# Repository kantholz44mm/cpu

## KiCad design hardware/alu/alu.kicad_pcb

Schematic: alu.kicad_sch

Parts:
C1, C2, C3, C4, C5, C6, C7, C8, C9, C10, C11, C12, C13, C14, C15, C16, C17, C18, C19, C20, C21, C22, C23, C24, C25, C26, C27, C28, C29, C30, C31, C32, C33, C34, C35, C40, C41, C42, C43, C44, C45, C46, C47, C50, C51, C52, C53, C54, C55, C56, C57, C58, C59, C60, C61, C62, C63, C64, C65, C66, C67, C68, C69, C70, C71, C72, C73, C77, C78, C79, C80, C81, C82, C83, C84, C85, C90, C91, C92, C93, C94, C95: 330nF; C_0402_1005Metric; LCSC C77020
C86, C87, C88, C89: 22pF; C_Radial_D5.0mm_H11.0mm_P2.00mm; not fitted
D30, D31, D32, D33, D34, D35, D36, D37, D38, D39, D40, D41, D42, D43, D44, D45, D46, D47, D48, D49, D50, D51, D52, D63, D89, D90, D91, D92, D93, D137, D138, D139, D140, D141, D142, D143, D144, D145, D146, D147, D148, D149, D150: LED; LED_0402_1005Metric; LCSC C965793
D124, D125, D126, D127, D128, D129, D130, D131: D_Schottky; DO35_Packed; not fitted
H1, H2, H3: MountingHole_Pad; MountingHole_3.2mm_M3_ISO7380_Pad_TopBottom
J8: Conn_02x24_Odd_Even; PinHeader_2x24_P2.54mm_Horizontal; not fitted
Q93, Q96, Q98, Q100, Q102, Q104, Q106, Q108, Q110, Q112, Q114, Q116, Q118, Q120, Q122, Q124, Q126, Q128, Q130, Q132, Q134, Q136, Q138, Q140, Q142, Q144, Q146, Q148, Q150, Q152, Q154, Q156, Q158, Q160, Q162, Q164, Q166, Q168, Q170, Q172, Q174, Q176: IRLML6402; SOT-23; LCSC C2886430
Q94, Q95, Q97, Q99, Q101, Q103, Q105, Q107, Q109, Q111, Q113, Q115, Q117, Q119, Q121, Q123, Q125, Q127, Q129, Q131, Q133, Q135, Q137, Q139, Q141, Q143, Q145, Q147, Q149, Q151, Q153, Q155, Q157, Q159, Q161, Q163, Q165, Q167, Q169, Q171, Q173, Q175: IRLML6244; SOT-23; LCSC C5123965
R1, R2, R3, R4, R5, R6, R7, R8, R9, R10, R11, R12, R13, R14, R15, R16, R17, R18, R19, R20, R21: 100K; R_0402_1005Metric; LCSC C60491
R107, R108, R109, R110, R111, R112, R113, R114, R115, R116, R117, R118, R119, R120, R121, R122, R123, R124, R125, R126, R127, R128, R129, R130, R131, R132, R133, R134, R135, R136, R137, R138, R139, R140, R141, R142, R143, R144, R145, R146, R147, R148, R149, R150, R151, R152, R153, R154, R155, R156, R157, R158, R159, R160, R161, R162, R163, R164, R165, R166, R167, R168, R169, R170, R171, R172, R173, R174, R175, R176, R177, R178, R179, R180, R181, R182, R183, R184, R185, R186, R187, R188, R189, R190, R191, R192: 1000; R_0402_1005Metric; LCSC C106235
U1, U2, U3, U4, U5, U6, U7, U8, U9, U10, U11, U12, U13, U14, U15, U16, U17, U18, U19, U20, U21, U22, U23, U24, U25, U26, U27, U28, U29, U30, U31, U32, U33, U34, U35, U36, U37, U38, U39, U40, U41, U44, U45, U46, U47, U48, U49, U56, U57, U64, U65, U72, U73, U74, U75, U83, U87: 74HC00; SOIC-14_3.9x8.7mm_P1.27mm; LCSC C5586
U42, U43, U50, U51, U52, U53, U54, U55, U58, U59, U60, U61, U62, U63, U66, U67, U71, U84, U85, U86, U88, U89, U90, U91: 74LS157; SOIC-16_3.9x9.9mm_P1.27mm; LCSC C6823
U68: 74HCT238; SOIC-16_3.9x9.9mm_P1.27mm; LCSC C5620

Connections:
+5V: C1.1, C2.1, C3.1, C4.1, C5.1, C6.1, C7.1, C8.1, C9.1, C10.1, C11.1, C12.1, C13.1, C14.1, C15.1, C16.1, C17.1, C18.1, C19.1, C20.1, C21.1, C22.1, C23.1, C24.1, C25.1, C26.1, C27.1, C28.1, C29.1, C30.1, C31.1, C32.1, C33.1, C34.1, C35.1, C40.1, C41.1, C42.1, C43.1, C44.1, C45.1, C46.1, C47.1, C50.1, C51.1, C52.1, C53.1, C54.1, C55.1, C56.1, C57.1, C58.1, C59.1, C60.1, C61.1, C62.1, C63.1, C64.1, C65.1, C66.1, C67.1, C68.1, C69.1, C70.1, C71.1, C72.1, C73.1, C77.1, C78.1, C79.1, C80.1, C81.1, C82.1, C83.1, C84.1, C85.1, C86.1, C87.1, C88.1, C89.1, C90.1, C91.1, C92.1, C93.1, C94.1, C95.1, D52.2 (A), J8.44, J8.46, Q93.2 (S), Q96.2 (S), Q98.2 (S), Q100.2 (S), Q102.2 (S), Q104.2 (S), Q106.2 (S), Q108.2 (S), Q110.2 (S), Q112.2 (S), Q114.2 (S), Q116.2 (S), Q118.2 (S), Q120.2 (S), Q122.2 (S), Q124.2 (S), Q126.2 (S), Q128.2 (S), Q130.2 (S), Q132.2 (S), Q134.2 (S), Q136.2 (S), Q138.2 (S), Q140.2 (S), Q142.2 (S), Q144.2 (S), Q146.2 (S), Q148.2 (S), Q150.2 (S), Q152.2 (S), Q154.2 (S), Q156.2 (S), Q158.2 (S), Q160.2 (S), Q162.2 (S), Q164.2 (S), Q166.2 (S), Q168.2 (S), Q170.2 (S), Q172.2 (S), Q174.2 (S), Q176.2 (S), R107.2, R108.2, R109.2, R110.2, R111.2, R112.2, R113.2, R114.2, R115.2, R116.2, R117.2, R118.2, R119.2, R120.2, R121.2, R122.2, R123.2, R124.2, R125.2, R126.2, R127.2, R128.2, R129.2, R130.2, R131.2, R132.2, R133.2, R134.2, R135.2, R136.2, R137.2, R138.2, R139.2, R140.2, R141.2, R142.2, R144.2, R146.2, R184.2, R186.2, R188.2, R190.2, U1.14 (VCC), U2.14 (VCC), U3.14 (VCC), U4.14 (VCC), U5.14 (VCC), U6.14 (VCC), U7.14 (VCC), U8.14 (VCC), U9.14 (VCC), U10.14 (VCC), U11.14 (VCC), U12.14 (VCC), U13.14 (VCC), U14.14 (VCC), U15.14 (VCC), U16.14 (VCC), U17.14 (VCC), U18.14 (VCC), U19.14 (VCC), U20.14 (VCC), U21.14 (VCC), U22.14 (VCC), U23.14 (VCC), U24.14 (VCC), U25.14 (VCC), U26.14 (VCC), U27.14 (VCC), U28.14 (VCC), U29.14 (VCC), U30.14 (VCC), U31.14 (VCC), U32.14 (VCC), U33.14 (VCC), U34.14 (VCC), U35.14 (VCC), U36.14 (VCC), U37.14 (VCC), U38.14 (VCC), U39.14 (VCC), U40.14 (VCC), U41.14 (VCC), U42.16 (VCC), U43.16 (VCC), U44.14 (VCC), U45.14 (VCC), U46.14 (VCC), U47.14 (VCC), U48.14 (VCC), U49.14 (VCC), U50.16 (VCC), U51.16 (VCC), U52.16 (VCC), U53.16 (VCC), U54.16 (VCC), U55.16 (VCC), U56.14 (VCC), U57.14 (VCC), U58.16 (VCC), U59.16 (VCC), U60.16 (VCC), U61.16 (VCC), U62.16 (VCC), U63.16 (VCC), U64.14 (VCC), U65.14 (VCC), U66.16 (VCC), U67.16 (VCC), U68.6 (E3), U68.16 (VCC), U71.16 (VCC), U72.14 (VCC), U73.14 (VCC), U74.14 (VCC), U75.14 (VCC), U83.14 (VCC), U84.16 (VCC), U85.16 (VCC), U86.16 (VCC), U87.14 (VCC), U88.16 (VCC), U89.16 (VCC), U90.16 (VCC), U91.16 (VCC)
/A0: J8.3, Q94.1 (G), R1.1
/A1: J8.5, Q95.1 (G), R3.1
/A2: J8.7, Q97.1 (G), R2.1
/A3: J8.9, Q99.1 (G), R4.1
/A4: J8.13, Q101.1 (G), R5.1
/A5: J8.15, Q103.1 (G), R6.1
/A6: J8.17, Q105.1 (G), R7.1
/A7: J8.19, Q107.1 (G), R8.1
/B0: J8.4, Q109.1 (G), R21.1
/B1: J8.6, Q111.1 (G), R20.1
/B2: J8.8, Q113.1 (G), R19.1
/B3: J8.10, Q115.1 (G), R18.1
/B4: J8.14, Q117.1 (G), R17.1
/B5: J8.16, Q119.1 (G), R16.1
/B6: J8.18, Q121.1 (G), R15.1
/B7: J8.20, Q123.1 (G), R14.1
/CEN: J8.35, Q125.1 (G), R12.1
/CIN: J8.33, Q127.1 (G), R13.1
/COUT: D50.2 (A), J8.27, Q174.3 (D)
/IA0: D35.2 (A), Q93.3 (D), U1.1, U1.4, U36.1, U36.2, U44.1, U44.4, U54.2 (I0a), U54.6 (I1b), U62.2 (I0a), U87.10
/IA1: D36.2 (A), Q96.3 (D), U5.1, U5.4, U37.1, U37.2, U45.1, U45.4, U54.5 (I0b), U54.10 (I1c), U62.3 (I1a), U62.5 (I0b)
/IA2: D37.2 (A), Q98.3 (D), U9.1, U9.4, U38.1, U38.2, U46.1, U46.4, U54.11 (I0c), U54.13 (I1d), U62.6 (I1b), U62.11 (I0c)
/IA3: D38.2 (A), Q100.3 (D), U13.1, U13.4, U39.1, U39.2, U47.1, U47.4, U54.14 (I0d), U55.3 (I1a), U62.10 (I1c), U62.14 (I0d)
/IA4: D39.2 (A), Q102.3 (D), U17.1, U17.4, U40.1, U40.2, U48.1, U48.4, U55.2 (I0a), U55.6 (I1b), U62.13 (I1d), U63.2 (I0a)
/IA5: D40.2 (A), Q104.3 (D), U21.1, U21.4, U55.5 (I0b), U55.10 (I1c), U56.1, U56.2, U63.3 (I1a), U63.5 (I0b), U64.1, U64.4
/IA6: D41.2 (A), Q106.3 (D), U25.1, U25.4, U41.1, U41.2, U49.1, U49.4, U55.11 (I0c), U55.13 (I1d), U63.6 (I1b), U63.11 (I0c)
/IA7: D42.2 (A), Q108.3 (D), U29.1, U29.4, U55.14 (I0d), U57.1, U57.2, U63.10 (I1c), U63.14 (I0d), U65.1, U65.4, U87.4
/IB0: D141.2 (A), Q110.3 (D), U4.1, U4.4, U36.4, U36.5, U44.2, U44.10, U54.1 (S), U55.1 (S), U62.1 (S), U63.1 (S)
/IB1: D140.2 (A), Q112.3 (D), U8.1, U8.4, U37.4, U37.5, U45.2, U45.10, U58.1 (S), U59.1 (S), U66.1 (S), U67.1 (S)
/IB2: D139.2 (A), Q114.3 (D), U12.1, U12.4, U38.4, U38.5, U46.2, U46.10, U60.1 (S), U61.1 (S), U71.1 (S), U84.1 (S)
/IB3: D138.2 (A), Q116.3 (D), U16.1, U16.4, U39.4, U39.5, U47.2, U47.10
/IB4: D137.2 (A), Q118.3 (D), U20.1, U20.4, U40.4, U40.5, U48.2, U48.10
/IB5: D45.2 (A), Q120.3 (D), U24.1, U24.4, U56.4, U56.5, U64.2, U64.10
/IB6: D44.2 (A), Q122.3 (D), U28.1, U28.4, U41.4, U41.5, U49.2, U49.10
/IB7: D43.2 (A), Q124.3 (D), U32.1, U32.4, U57.4, U57.5, U65.2, U65.10
/ICEN: D33.2 (A), Q126.3 (D), U83.2
/ICIN: D34.2 (A), Q128.3 (D), U83.1
/ICRY: D144.2 (A), Q152.3 (D), U33.1, U33.4, U54.3 (I1a), U58.3 (I1a), U58.6 (I1b), U60.3 (I1a), U60.6 (I1b), U60.10 (I1c), U60.13 (I1d), U63.13 (I1d), U67.10 (I1c), U67.13 (I1d), U84.3 (I1a), U84.6 (I1b), U84.10 (I1c), U84.13 (I1d)
/IOP0: D30.2 (A), Q130.3 (D), U4.2, U4.10, U8.2, U8.10, U12.2, U12.10, U16.2, U16.10, U20.2, U20.10, U24.2, U24.10, U28.2, U28.10, U32.2, U32.10, U33.2, U33.10, U35.2, U35.10, U42.1 (S), U43.1 (S), U51.1 (S), U53.1 (S), U68.1 (A0), U85.1 (S), U86.1 (S), U87.1, U87.2, U87.9
/IOP1: D31.2 (A), Q132.3 (D), U50.1 (S), U52.1 (S), U68.2 (A1), U72.10, U72.12, U72.13, U75.4, U75.5, U90.1 (S), U91.1 (S)
/IOP2: D32.2 (A), Q134.3 (D), U68.3 (A2), U73.10, U73.12, U73.13, U75.9, U75.10, U88.1 (S), U89.1 (S)
/IOPSEL0: D63.2 (A), Q136.3 (D)
/IOPSEL1: D89.2 (A), Q138.3 (D)
/IOPSEL2: D90.2 (A), Q140.3 (D)
/IOPSEL3: D91.2 (A), Q142.3 (D)
/IOPSEL4: D92.2 (A), Q144.3 (D)
/IOPSEL5: D93.2 (A), Q146.3 (D)
/IOPSEL6: D142.2 (A), Q148.3 (D)
/IOPSEL7: D143.2 (A), Q150.3 (D)
/NEG: D49.2 (A), J8.25, Q172.3 (D)
/OP0: J8.39, Q129.1 (G), R9.1
/OP1: J8.41, Q131.1 (G), R10.1
/OP2: J8.43, Q133.1 (G), R11.1
/ORES0: D48.2 (A), D128.2 (A), J8.24, Q168.3 (D)
/ORES1: D47.2 (A), D129.2 (A), J8.26, Q166.3 (D)
/ORES2: D46.2 (A), D130.2 (A), J8.28, Q164.3 (D)
/ORES3: D131.2 (A), D149.2 (A), J8.30, Q162.3 (D)
/ORES4: D127.2 (A), D148.2 (A), J8.34, Q160.3 (D)
/ORES5: D126.2 (A), D147.2 (A), J8.36, Q158.3 (D)
/ORES6: D125.2 (A), D146.2 (A), J8.38, Q156.3 (D)
/ORES7: D124.2 (A), D145.2 (A), J8.40, Q154.3 (D), Q171.1 (G)
/OVF: D51.2 (A), J8.29, Q176.3 (D)
/ZERO: D150.2 (A), J8.23, Q170.3 (D)
GND: C1.2, C2.2, C3.2, C4.2, C5.2, C6.2, C7.2, C8.2, C9.2, C10.2, C11.2, C12.2, C13.2, C14.2, C15.2, C16.2, C17.2, C18.2, C19.2, C20.2, C21.2, C22.2, C23.2, C24.2, C25.2, C26.2, C27.2, C28.2, C29.2, C30.2, C31.2, C32.2, C33.2, C34.2, C35.2, C40.2, C41.2, C42.2, C43.2, C44.2, C45.2, C46.2, C47.2, C50.2, C51.2, C52.2, C53.2, C54.2, C55.2, C56.2, C57.2, C58.2, C59.2, C60.2, C61.2, C62.2, C63.2, C64.2, C65.2, C66.2, C67.2, C68.2, C69.2, C70.2, C71.2, C72.2, C73.2, C77.2, C78.2, C79.2, C80.2, C81.2, C82.2, C83.2, C84.2, C85.2, C86.2, C87.2, C88.2, C89.2, C90.2, C91.2, C92.2, C93.2, C94.2, C95.2, H1.1, H2.1, H3.1, J8.1, J8.2, J8.11, J8.12, J8.21, J8.22, J8.31, J8.32, J8.37, J8.42, J8.45, J8.47, J8.48, Q94.2 (S), Q95.2 (S), Q97.2 (S), Q99.2 (S), Q101.2 (S), Q103.2 (S), Q105.2 (S), Q107.2 (S), Q109.2 (S), Q111.2 (S), Q113.2 (S), Q115.2 (S), Q117.2 (S), Q119.2 (S), Q121.2 (S), Q123.2 (S), Q125.2 (S), Q127.2 (S), Q129.2 (S), Q131.2 (S), Q133.2 (S), Q135.2 (S), Q137.2 (S), Q139.2 (S), Q141.2 (S), Q143.2 (S), Q145.2 (S), Q147.2 (S), Q149.2 (S), Q151.2 (S), Q153.2 (S), Q155.2 (S), Q157.2 (S), Q159.2 (S), Q161.2 (S), Q163.2 (S), Q165.2 (S), Q167.2 (S), Q169.2 (S), Q171.2 (S), Q173.2 (S), Q175.2 (S), R1.2, R2.2, R3.2, R4.2, R5.2, R6.2, R7.2, R8.2, R9.2, R10.2, R11.2, R12.2, R13.2, R14.2, R15.2, R16.2, R17.2, R18.2, R19.2, R20.2, R21.2, R143.1, R145.1, R147.1, R148.1, R149.1, R150.1, R151.1, R152.1, R153.1, R154.1, R155.1, R156.1, R157.1, R158.1, R159.1, R160.1, R161.1, R162.1, R163.1, R164.1, R165.1, R166.1, R167.1, R168.1, R169.1, R170.1, R171.1, R172.1, R173.1, R174.1, R175.1, R176.1, R177.1, R178.1, R179.1, R180.1, R181.1, R182.1, R183.1, R185.1, R187.1, R189.1, R191.1, R192.1, U1.7 (GND), U2.7 (GND), U3.4, U3.5, U3.7 (GND), U3.9, U3.10, U3.12, U3.13, U4.7 (GND), U5.7 (GND), U6.7 (GND), U7.4, U7.5, U7.7 (GND), U7.9, U7.10, U7.12, U7.13, U8.7 (GND), U9.7 (GND), U10.7 (GND), U11.4, U11.5, U11.7 (GND), U11.9, U11.10, U11.12, U11.13, U12.7 (GND), U13.7 (GND), U14.7 (GND), U15.4, U15.5, U15.7 (GND), U15.9, U15.10, U15.12, U15.13, U16.7 (GND), U17.7 (GND), U18.7 (GND), U19.4, U19.5, U19.7 (GND), U19.9, U19.10, U19.12, U19.13, U20.7 (GND), U21.7 (GND), U22.7 (GND), U23.4, U23.5, U23.7 (GND), U23.9, U23.10, U23.12, U23.13, U24.7 (GND), U25.7 (GND), U26.7 (GND), U27.4, U27.5, U27.7 (GND), U27.9, U27.10, U27.12, U27.13, U28.7 (GND), U29.7 (GND), U30.7 (GND), U31.4, U31.5, U31.7 (GND), U31.9, U31.10, U31.12, U31.13, U32.7 (GND), U33.7 (GND), U34.7 (GND), U35.7 (GND), U36.7 (GND), U37.7 (GND), U38.7 (GND), U39.7 (GND), U40.7 (GND), U41.7 (GND), U42.8 (GND), U42.15 (E), U43.8 (GND), U43.15 (E), U44.7 (GND), U45.7 (GND), U46.7 (GND), U47.7 (GND), U48.7 (GND), U49.7 (GND), U50.8 (GND), U50.15 (E), U51.8 (GND), U51.15 (E), U52.8 (GND), U52.15 (E), U53.8 (GND), U53.15 (E), U54.8 (GND), U54.15 (E), U55.8 (GND), U55.15 (E), U56.7 (GND), U57.7 (GND), U58.8 (GND), U58.15 (E), U59.8 (GND), U59.15 (E), U60.8 (GND), U60.15 (E), U61.8 (GND), U61.15 (E), U62.8 (GND), U62.15 (E), U63.8 (GND), U63.15 (E), U64.7 (GND), U65.7 (GND), U66.8 (GND), U66.15 (E), U67.8 (GND), U67.15 (E), U68.4 (~E1), U68.5 (~E2), U68.8 (GND), U71.8 (GND), U71.15 (E), U72.7 (GND), U73.7 (GND), U73.9, U74.7 (GND), U74.9, U75.7 (GND), U83.7 (GND), U83.9, U83.10, U83.12, U83.13, U84.8 (GND), U84.15 (E), U85.8 (GND), U85.15 (E), U86.8 (GND), U86.15 (E), U87.7 (GND), U88.8 (GND), U88.15 (E), U89.8 (GND), U89.15 (E), U90.8 (GND), U90.15 (E), U91.8 (GND), U91.15 (E)
unnamed: D30.1 (K), R143.2
unnamed: D31.1 (K), R145.2
unnamed: D32.1 (K), R147.2
unnamed: D33.1 (K), R148.2
unnamed: D34.1 (K), R149.2
unnamed: D35.1 (K), R150.2
unnamed: D36.1 (K), R151.2
unnamed: D37.1 (K), R152.2
unnamed: D38.1 (K), R153.2
unnamed: D39.1 (K), R154.2
unnamed: D40.1 (K), R155.2
unnamed: D41.1 (K), R156.2
unnamed: D42.1 (K), R157.2
unnamed: D43.1 (K), R158.2
unnamed: D44.1 (K), R159.2
unnamed: D45.1 (K), R160.2
unnamed: D46.1 (K), R180.2
unnamed: D47.1 (K), R181.2
unnamed: D48.1 (K), R182.2
unnamed: D49.1 (K), R187.2
unnamed: D50.1 (K), R189.2
unnamed: D51.1 (K), R191.2
unnamed: D52.1 (K), R192.2
unnamed: D63.1 (K), R166.2
unnamed: D89.1 (K), R167.2
unnamed: D90.1 (K), R168.2
unnamed: D91.1 (K), R169.2
unnamed: D92.1 (K), R170.2
unnamed: D93.1 (K), R171.2
unnamed: D124.1 (K), D125.1 (K), D126.1 (K), D127.1 (K), D128.1 (K), D129.1 (K), D130.1 (K), D131.1 (K), R183.2, U75.12, U75.13
unnamed: D137.1 (K), R161.2
unnamed: D138.1 (K), R162.2
unnamed: D139.1 (K), R163.2
unnamed: D140.1 (K), R164.2
unnamed: D141.1 (K), R165.2
unnamed: D142.1 (K), R172.2
unnamed: D143.1 (K), R173.2
unnamed: D144.1 (K), R174.2
unnamed: D145.1 (K), R175.2
unnamed: D146.1 (K), R176.2
unnamed: D147.1 (K), R177.2
unnamed: D148.1 (K), R178.2
unnamed: D149.1 (K), R179.2
unnamed: D150.1 (K), R185.2
unnamed: Q93.1 (G), Q94.3 (D), R107.1
unnamed: Q95.3 (D), Q96.1 (G), R108.1
unnamed: Q97.3 (D), Q98.1 (G), R110.1
unnamed: Q99.3 (D), Q100.1 (G), R112.1
unnamed: Q101.3 (D), Q102.1 (G), R114.1
unnamed: Q103.3 (D), Q104.1 (G), R116.1
unnamed: Q105.3 (D), Q106.1 (G), R118.1
unnamed: Q107.3 (D), Q108.1 (G), R120.1
unnamed: Q109.3 (D), Q110.1 (G), R122.1
unnamed: Q111.3 (D), Q112.1 (G), R124.1
unnamed: Q113.3 (D), Q114.1 (G), R126.1
unnamed: Q115.3 (D), Q116.1 (G), R128.1
unnamed: Q117.3 (D), Q118.1 (G), R130.1
unnamed: Q119.3 (D), Q120.1 (G), R132.1
unnamed: Q121.3 (D), Q122.1 (G), R134.1
unnamed: Q123.3 (D), Q124.1 (G), R136.1
unnamed: Q125.3 (D), Q126.1 (G), R138.1
unnamed: Q127.3 (D), Q128.1 (G), R140.1
unnamed: Q129.3 (D), Q130.1 (G), R142.1
unnamed: Q131.3 (D), Q132.1 (G), R144.1
unnamed: Q133.3 (D), Q134.1 (G), R146.1
unnamed: Q135.3 (D), Q136.1 (G), R109.1
unnamed: Q135.1 (G), U68.15 (Y0)
unnamed: Q137.3 (D), Q138.1 (G), R111.1
unnamed: Q137.1 (G), U68.14 (Y1)
unnamed: Q139.3 (D), Q140.1 (G), R113.1
unnamed: Q139.1 (G), U68.13 (Y2)
unnamed: Q141.3 (D), Q142.1 (G), R115.1
unnamed: Q141.1 (G), U68.12 (Y3)
unnamed: Q143.3 (D), Q144.1 (G), R117.1
unnamed: Q143.1 (G), U68.11 (Y4)
unnamed: Q145.3 (D), Q146.1 (G), R119.1
unnamed: Q145.1 (G), U68.10 (Y5)
unnamed: Q147.3 (D), Q148.1 (G), R121.1
unnamed: Q147.1 (G), U68.9 (Y6)
unnamed: Q149.3 (D), Q150.1 (G), R123.1
unnamed: Q149.1 (G), U68.7 (Y7)
unnamed: Q151.3 (D), Q152.1 (G), R141.1
unnamed: Q151.1 (G), U83.6
unnamed: Q153.3 (D), Q154.1 (G), R125.1
unnamed: Q153.1 (G), U89.12 (Zd)
unnamed: Q155.3 (D), Q156.1 (G), R127.1
unnamed: Q155.1 (G), U89.9 (Zc)
unnamed: Q157.3 (D), Q158.1 (G), R129.1
unnamed: Q157.1 (G), U89.7 (Zb)
unnamed: Q159.3 (D), Q160.1 (G), R131.1
unnamed: Q159.1 (G), U89.4 (Za)
unnamed: Q161.3 (D), Q162.1 (G), R133.1
unnamed: Q161.1 (G), U88.12 (Zd)
unnamed: Q163.3 (D), Q164.1 (G), R135.1
unnamed: Q163.1 (G), U88.9 (Zc)
unnamed: Q165.3 (D), Q166.1 (G), R137.1
unnamed: Q165.1 (G), U88.7 (Zb)
unnamed: Q167.3 (D), Q168.1 (G), R139.1
unnamed: Q167.1 (G), U88.4 (Za)
unnamed: Q169.3 (D), Q170.1 (G), R184.1
unnamed: Q169.1 (G), U75.11
unnamed: Q171.3 (D), Q172.1 (G), R186.1
unnamed: Q173.3 (D), Q174.1 (G), R188.1
unnamed: Q173.1 (G), U73.3
unnamed: Q175.3 (D), Q176.1 (G), R190.1
unnamed: Q175.1 (G), U74.3
unnamed: U1.3, U1.5, U1.9, U3.2
unnamed: U1.2, U1.10, U4.11
unnamed: U1.11, U2.1, U2.4
unnamed: U1.6, U1.12
unnamed: U1.8, U1.13
unnamed: U2.3, U2.5, U2.9, U3.1
unnamed: U2.2, U2.10, U33.11
unnamed: U2.6, U2.12
unnamed: U2.8, U2.13
unnamed: U3.3, U6.2, U6.10
unnamed: U4.3, U4.5, U4.9
unnamed: U4.6, U4.12
unnamed: U4.8, U4.13
unnamed: U5.3, U5.5, U5.9, U7.2
unnamed: U5.2, U5.10, U8.11
unnamed: U5.11, U6.1, U6.4
unnamed: U5.6, U5.12
unnamed: U5.8, U5.13
unnamed: U6.3, U6.5, U6.9, U7.1
unnamed: U6.6, U6.12
unnamed: U6.8, U6.13
unnamed: U8.3, U8.5, U8.9
unnamed: U8.6, U8.12
unnamed: U8.8, U8.13
unnamed: U9.6, U9.12
unnamed: U9.8, U9.13
unnamed: U9.11, U10.1, U10.4
unnamed: U10.3, U10.5, U10.9, U11.1
unnamed: U7.3, U10.2, U10.10
unnamed: U10.6, U10.12
unnamed: U10.8, U10.13
unnamed: U9.3, U9.5, U9.9, U11.2
unnamed: U11.3, U14.2, U14.10
unnamed: U12.3, U12.5, U12.9
unnamed: U9.2, U9.10, U12.11
unnamed: U12.6, U12.12
unnamed: U12.8, U12.13
unnamed: U13.3, U13.5, U13.9, U15.2
unnamed: U13.2, U13.10, U16.11
unnamed: U13.11, U14.1, U14.4
unnamed: U13.6, U13.12
unnamed: U13.8, U13.13
unnamed: U14.3, U14.5, U14.9, U15.1
unnamed: U14.6, U14.12
unnamed: U14.8, U14.13
unnamed: U15.3, U18.2, U18.10
unnamed: U16.3, U16.5, U16.9
unnamed: U16.6, U16.12
unnamed: U16.8, U16.13
unnamed: U17.3, U17.5, U17.9, U19.2
unnamed: U17.2, U17.10, U20.11
unnamed: U17.11, U18.1, U18.4
unnamed: U17.6, U17.12
unnamed: U17.8, U17.13
unnamed: U18.3, U18.5, U18.9, U19.1
unnamed: U18.6, U18.12
unnamed: U18.8, U18.13
unnamed: U19.3, U22.2, U22.10
unnamed: U20.3, U20.5, U20.9
unnamed: U20.6, U20.12
unnamed: U20.8, U20.13
unnamed: U21.3, U21.5, U21.9, U23.2
unnamed: U21.2, U21.10, U24.11
unnamed: U21.11, U22.1, U22.4
unnamed: U21.6, U21.12
unnamed: U21.8, U21.13
unnamed: U22.3, U22.5, U22.9, U23.1
unnamed: U22.6, U22.12
unnamed: U22.8, U22.13
unnamed: U23.3, U26.2, U26.10
unnamed: U24.3, U24.5, U24.9
unnamed: U24.6, U24.12
unnamed: U24.8, U24.13
unnamed: U25.3, U25.5, U25.9, U27.2
unnamed: U25.2, U25.10, U28.11
unnamed: U25.11, U26.1, U26.4
unnamed: U25.6, U25.12
unnamed: U25.8, U25.13
unnamed: U26.3, U26.5, U26.9, U27.1
unnamed: U26.6, U26.12
unnamed: U26.8, U26.13
unnamed: U27.3, U30.2, U30.10, U34.2, U34.10
unnamed: U28.3, U28.5, U28.9
unnamed: U28.6, U28.12
unnamed: U28.8, U28.13
unnamed: U29.3, U29.5, U29.9, U31.2
unnamed: U29.2, U29.10, U32.11
unnamed: U29.11, U30.1, U30.4
unnamed: U29.6, U29.12
unnamed: U29.8, U29.13
unnamed: U30.3, U30.5, U30.9, U31.1
unnamed: U30.6, U30.12
unnamed: U30.8, U30.13
unnamed: U31.3, U34.1, U34.4, U35.1, U35.4
unnamed: U32.3, U32.5, U32.9
unnamed: U32.6, U32.12
unnamed: U32.8, U32.13
unnamed: U33.3, U33.5, U33.9
unnamed: U33.6, U33.12
unnamed: U33.8, U33.13
unnamed: U34.3, U34.5, U34.9
unnamed: U34.11, U74.5
unnamed: U34.6, U34.12
unnamed: U34.8, U34.13
unnamed: U35.3, U35.5, U35.9
unnamed: U35.11, U72.5
unnamed: U35.6, U35.12
unnamed: U35.8, U35.13
unnamed: U36.3, U36.9
unnamed: U36.6, U36.10
unnamed: U37.3, U37.9
unnamed: U37.6, U37.10
unnamed: U38.3, U38.9
unnamed: U38.6, U38.10
unnamed: U39.3, U39.9
unnamed: U39.6, U39.10
unnamed: U40.3, U40.9
unnamed: U40.6, U40.10
unnamed: U41.3, U41.9
unnamed: U41.6, U41.10
unnamed: U39.8, U42.2 (I0a)
unnamed: U38.8, U42.5 (I0b)
unnamed: U37.8, U42.11 (I0c)
unnamed: U36.8, U42.14 (I0d)
unnamed: U39.11, U42.3 (I1a)
unnamed: U38.11, U42.6 (I1b)
unnamed: U37.11, U42.10 (I1c)
unnamed: U36.11, U42.13 (I1d)
unnamed: U42.4 (Za), U50.2 (I0a)
unnamed: U42.7 (Zb), U50.5 (I0b)
unnamed: U42.9 (Zc), U50.11 (I0c)
unnamed: U42.12 (Zd), U50.14 (I0d)
unnamed: U43.2 (I0a), U47.11
unnamed: U43.5 (I0b), U46.11
unnamed: U43.11 (I0c), U45.11
unnamed: U43.14 (I0d), U44.11
unnamed: U39.12, U39.13, U43.3 (I1a), U47.3, U47.5, U47.9
unnamed: U38.12, U38.13, U43.6 (I1b), U46.3, U46.5, U46.9
unnamed: U37.12, U37.13, U43.10 (I1c), U45.3, U45.5, U45.9
unnamed: U36.12, U36.13, U43.13 (I1d), U44.3, U44.5, U44.9
unnamed: U43.4 (Za), U50.3 (I1a)
unnamed: U43.7 (Zb), U50.6 (I1b)
unnamed: U43.9 (Zc), U50.10 (I1c)
unnamed: U43.12 (Zd), U50.13 (I1d)
unnamed: U44.6, U44.12
unnamed: U44.8, U44.13
unnamed: U45.6, U45.12
unnamed: U45.8, U45.13
unnamed: U46.6, U46.12
unnamed: U46.8, U46.13
unnamed: U47.6, U47.12
unnamed: U47.8, U47.13
unnamed: U48.6, U48.12
unnamed: U48.8, U48.13
unnamed: U49.6, U49.12
unnamed: U49.8, U49.13
unnamed: U50.4 (Za), U88.13 (I1d)
unnamed: U50.7 (Zb), U88.10 (I1c)
unnamed: U50.9 (Zc), U88.6 (I1b)
unnamed: U50.12 (Zd), U88.3 (I1a)
unnamed: U51.2 (I0a), U57.8
unnamed: U41.8, U51.5 (I0b)
unnamed: U51.11 (I0c), U56.8
unnamed: U40.8, U51.14 (I0d)
unnamed: U51.3 (I1a), U57.11
unnamed: U41.11, U51.6 (I1b)
unnamed: U51.10 (I1c), U56.11
unnamed: U40.11, U51.13 (I1d)
unnamed: U51.4 (Za), U52.2 (I0a)
unnamed: U51.7 (Zb), U52.5 (I0b)
unnamed: U51.9 (Zc), U52.11 (I0c)
unnamed: U51.12 (Zd), U52.14 (I0d)
unnamed: U52.3 (I1a), U53.4 (Za)
unnamed: U52.6 (I1b), U53.7 (Zb)
unnamed: U52.10 (I1c), U53.9 (Zc)
unnamed: U52.13 (I1d), U53.12 (Zd)
unnamed: U52.4 (Za), U89.13 (I1d)
unnamed: U52.7 (Zb), U89.10 (I1c)
unnamed: U52.9 (Zc), U89.6 (I1b)
unnamed: U52.12 (Zd), U89.3 (I1a)
unnamed: U53.2 (I0a), U65.11
unnamed: U49.11, U53.5 (I0b)
unnamed: U53.11 (I0c), U64.11
unnamed: U48.11, U53.14 (I0d)
unnamed: U53.3 (I1a), U57.12, U57.13, U65.3, U65.5, U65.9
unnamed: U41.12, U41.13, U49.3, U49.5, U49.9, U53.6 (I1b)
unnamed: U53.10 (I1c), U56.12, U56.13, U64.3, U64.5, U64.9
unnamed: U40.12, U40.13, U48.3, U48.5, U48.9, U53.13 (I1d)
unnamed: U54.4 (Za), U58.2 (I0a), U58.10 (I1c)
unnamed: U54.7 (Zb), U58.5 (I0b), U58.13 (I1d)
unnamed: U54.9 (Zc), U58.11 (I0c), U59.3 (I1a)
unnamed: U54.12 (Zd), U58.14 (I0d), U59.6 (I1b)
unnamed: U55.4 (Za), U59.2 (I0a), U59.10 (I1c)
unnamed: U55.7 (Zb), U59.5 (I0b), U59.13 (I1d)
unnamed: U55.9 (Zc), U59.11 (I0c)
unnamed: U55.12 (Zd), U59.14 (I0d)
unnamed: U56.3, U56.9
unnamed: U56.6, U56.10
unnamed: U57.3, U57.9
unnamed: U57.6, U57.10
unnamed: U58.4 (Za), U60.2 (I0a), U61.3 (I1a)
unnamed: U58.7 (Zb), U60.5 (I0b), U61.6 (I1b)
unnamed: U58.9 (Zc), U60.11 (I0c), U61.10 (I1c)
unnamed: U58.12 (Zd), U60.14 (I0d), U61.13 (I1d)
unnamed: U59.4 (Za), U61.2 (I0a)
unnamed: U59.7 (Zb), U61.5 (I0b)
unnamed: U59.9 (Zc), U61.11 (I0c)
unnamed: U59.12 (Zd), U61.14 (I0d)
unnamed: U60.4 (Za), U86.14 (I0d)
unnamed: U60.7 (Zb), U86.11 (I0c)
unnamed: U60.9 (Zc), U86.5 (I0b)
unnamed: U60.12 (Zd), U86.2 (I0a)
unnamed: U61.4 (Za), U85.14 (I0d)
unnamed: U61.7 (Zb), U85.11 (I0c)
unnamed: U61.9 (Zc), U85.5 (I0b)
unnamed: U61.12 (Zd), U85.2 (I0a)
unnamed: U62.4 (Za), U66.2 (I0a)
unnamed: U62.7 (Zb), U66.5 (I0b)
unnamed: U62.9 (Zc), U66.3 (I1a), U66.11 (I0c)
unnamed: U62.12 (Zd), U66.6 (I1b), U66.14 (I0d)
unnamed: U63.4 (Za), U66.10 (I1c), U67.2 (I0a)
unnamed: U63.7 (Zb), U66.13 (I1d), U67.5 (I0b)
unnamed: U63.9 (Zc), U67.3 (I1a), U67.11 (I0c)
unnamed: U63.12 (Zd), U67.6 (I1b), U67.14 (I0d)
unnamed: U64.6, U64.12
unnamed: U64.8, U64.13
unnamed: U65.6, U65.12
unnamed: U65.8, U65.13
unnamed: U66.4 (Za), U71.2 (I0a)
unnamed: U66.7 (Zb), U71.5 (I0b)
unnamed: U66.9 (Zc), U71.11 (I0c)
unnamed: U66.12 (Zd), U71.14 (I0d)
unnamed: U67.4 (Za), U71.3 (I1a), U84.2 (I0a)
unnamed: U67.7 (Zb), U71.6 (I1b), U84.5 (I0b)
unnamed: U67.9 (Zc), U71.10 (I1c), U84.11 (I0c)
unnamed: U67.12 (Zd), U71.13 (I1d), U84.14 (I0d)
unnamed: U71.4 (Za), U86.13 (I1d)
unnamed: U71.7 (Zb), U86.10 (I1c)
unnamed: U71.9 (Zc), U86.6 (I1b)
unnamed: U71.12 (Zd), U86.3 (I1a)
unnamed: U72.1, U72.8
unnamed: U72.2, U72.6
unnamed: U72.3, U73.5
unnamed: U72.9, U87.11
unnamed: U72.4, U72.11
unnamed: U73.1, U73.8
unnamed: U73.2, U73.6
unnamed: U73.4, U73.11
unnamed: U74.1, U74.8
unnamed: U74.2, U74.6
unnamed: U74.10, U74.12, U74.13, U75.3
unnamed: U74.4, U74.11
unnamed: U75.1, U75.8
unnamed: U75.2, U75.6
unnamed: U83.3, U83.4, U83.5
unnamed: U84.4 (Za), U85.13 (I1d)
unnamed: U84.7 (Zb), U85.10 (I1c)
unnamed: U84.9 (Zc), U85.6 (I1b)
unnamed: U84.12 (Zd), U85.3 (I1a)
unnamed: U85.4 (Za), U91.13 (I1d)
unnamed: U85.7 (Zb), U91.10 (I1c)
unnamed: U85.9 (Zc), U91.6 (I1b)
unnamed: U85.12 (Zd), U91.3 (I1a)
unnamed: U86.4 (Za), U90.13 (I1d)
unnamed: U86.7 (Zb), U90.10 (I1c)
unnamed: U86.9 (Zc), U90.6 (I1b)
unnamed: U86.12 (Zd), U90.3 (I1a)
unnamed: U87.3, U87.5
unnamed: U87.6, U87.12
unnamed: U87.8, U87.13
unnamed: U88.2 (I0a), U90.4 (Za)
unnamed: U88.5 (I0b), U90.7 (Zb)
unnamed: U88.11 (I0c), U90.9 (Zc)
unnamed: U88.14 (I0d), U90.12 (Zd)
unnamed: U89.2 (I0a), U91.4 (Za)
unnamed: U89.5 (I0b), U91.7 (Zb)
unnamed: U89.11 (I0c), U91.9 (Zc)
unnamed: U89.14 (I0d), U91.12 (Zd)
unnamed: U2.11, U90.2 (I0a)
unnamed: U6.11, U90.5 (I0b)
unnamed: U10.11, U90.11 (I0c)
unnamed: U14.11, U90.14 (I0d)
unnamed: U18.11, U91.2 (I0a)
unnamed: U22.11, U91.5 (I0b)
unnamed: U26.11, U91.11 (I0c)
unnamed: U30.11, U91.14 (I0d)

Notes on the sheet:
Shift
Bitops
OVF
COUT
ADD/SUB

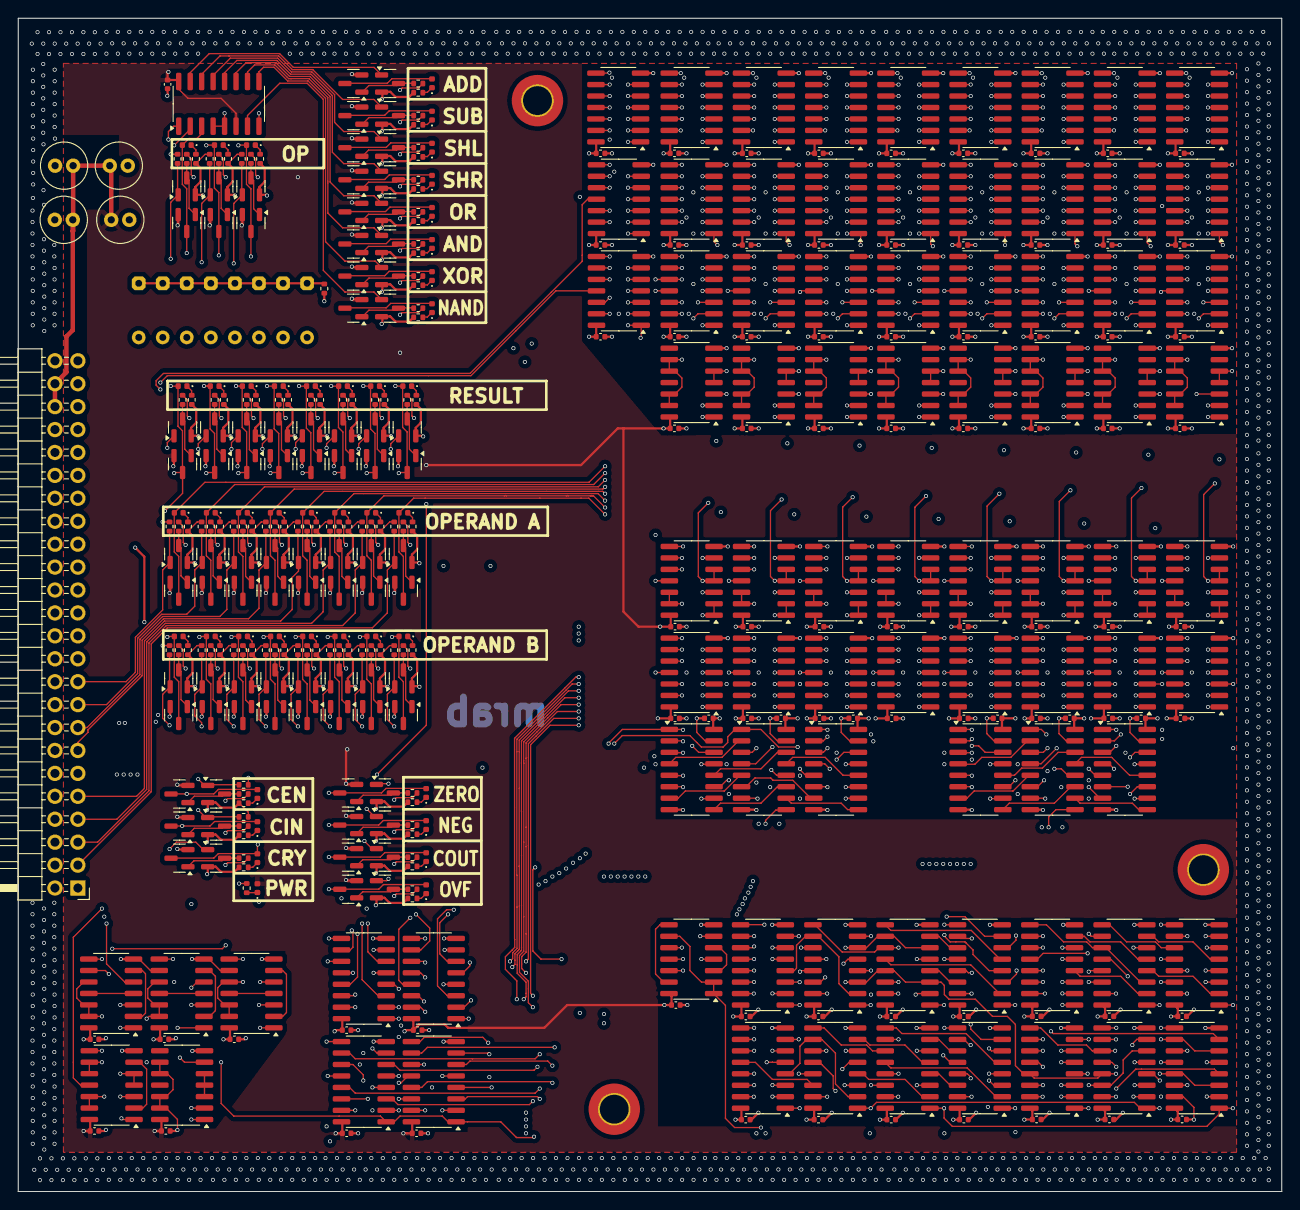
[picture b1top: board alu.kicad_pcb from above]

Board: 4 copper layers, 140.0 x 130.0 mm, 414 parts (0 on the bottom side), 457 nets.

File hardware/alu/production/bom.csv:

Designator,Footprint,Quantity,Value,LCSC Part #
"C1, C10, C11, C12, C13, C14, C15, C16, C17, C18, C19, C2, C20, C21, C22, C23, C24, C25, C26, C27, C28, C29, C3, C30, C31, C32, C33, C34, C35, C4, C40, C41, C42, C43, C44, C45, C46, C47, C5, C50, C51, C52, C53, C54, C55, C56, C57, C58, C59, C6, C60, C61, C62, C63, C64, C65, C66, C67, C68, C69, C7, C70, C71, C72, C73, C77, C78, C79, C8, C80, C81, C82, C83, C84, C85, C9, C90, C91, C92, C93, C94, C95",0402,82,330nF,C77020
"D137, D138, D139, D140, D141, D142, D143, D144, D145, D146, D147, D148, D149, D150, D30, D31, D32, D33, D34, D35, D36, D37, D38, D39, D40, D41, D42, D43, D44, D45, D46, D47, D48, D49, D50, D51, D52, D63, D89, D90, D91, D92, D93",0402,43,LED,C965793
"Q100, Q102, Q104, Q106, Q108, Q110, Q112, Q114, Q116, Q118, Q120, Q122, Q124, Q126, Q128, Q130, Q132, Q134, Q136, Q138, Q140, Q142, Q144, Q146, Q148, Q150, Q152, Q154, Q156, Q158, Q160, Q162, Q164, Q166, Q168, Q170, Q172, Q174, Q176, Q93, Q96, Q98",SOT-23,42,IRLML6402,C2886430
"Q101, Q103, Q105, Q107, Q109, Q111, Q113, Q115, Q117, Q119, Q121, Q123, Q125, Q127, Q129, Q131, Q133, Q135, Q137, Q139, Q141, Q143, Q145, Q147, Q149, Q151, Q153, Q155, Q157, Q159, Q161, Q163, Q165, Q167, Q169, Q171, Q173, Q175, Q94, Q95, Q97, Q99",SOT-23,42,IRLML6244,C5123965
"R1, R10, R11, R12, R13, R14, R15, R16, R17, R18, R19, R2, R20, R21, R3, R4, R5, R6, R7, R8, R9",0402,21,100K,C60491
"R107, R108, R109, R110, R111, R112, R113, R114, R115, R116, R117, R118, R119, R120, R121, R122, R123, R124, R125, R126, R127, R128, R129, R130, R131, R132, R133, R134, R135, R136, R137, R138, R139, R140, R141, R142, R143, R144, R145, R146, R147, R148, R149, R150, R151, R152, R153, R154, R155, R156, R157, R158, R159, R160, R161, R162, R163, R164, R165, R166, R167, R168, R169, R170, R171, R172, R173, R174, R175, R176, R177, R178, R179, R180, R181, R182, R183, R184, R185, R186, R187, R188, R189, R190, R191, R192",0402,86,1000,C106235
"U1, U10, U11, U12, U13, U14, U15, U16, U17, U18, U19, U2, U20, U21, U22, U23, U24, U25, U26, U27, U28, U29, U3, U30, U31, U32, U33, U34, U35, U36, U37, U38, U39, U4, U40, U41, U44, U45, U46, U47, U48, U49, U5, U56, U57, U6, U64, U65, U7, U72, U73, U74, U75, U8, U83, U87, U9",SOIC-14_3.9x8.7mm_P1.27mm,57,74HC00,C5586
"U42, U43, U50, U51, U52, U53, U54, U55, U58, U59, U60, U61, U62, U63, U66, U67, U71, U84, U85, U86, U88, U89, U90, U91",SOIC-16_3.9x9.9mm_P1.27mm,24,74LS157,C6823
U68,SOIC-16_3.9x9.9mm_P1.27mm,1,74HCT238,C5620
